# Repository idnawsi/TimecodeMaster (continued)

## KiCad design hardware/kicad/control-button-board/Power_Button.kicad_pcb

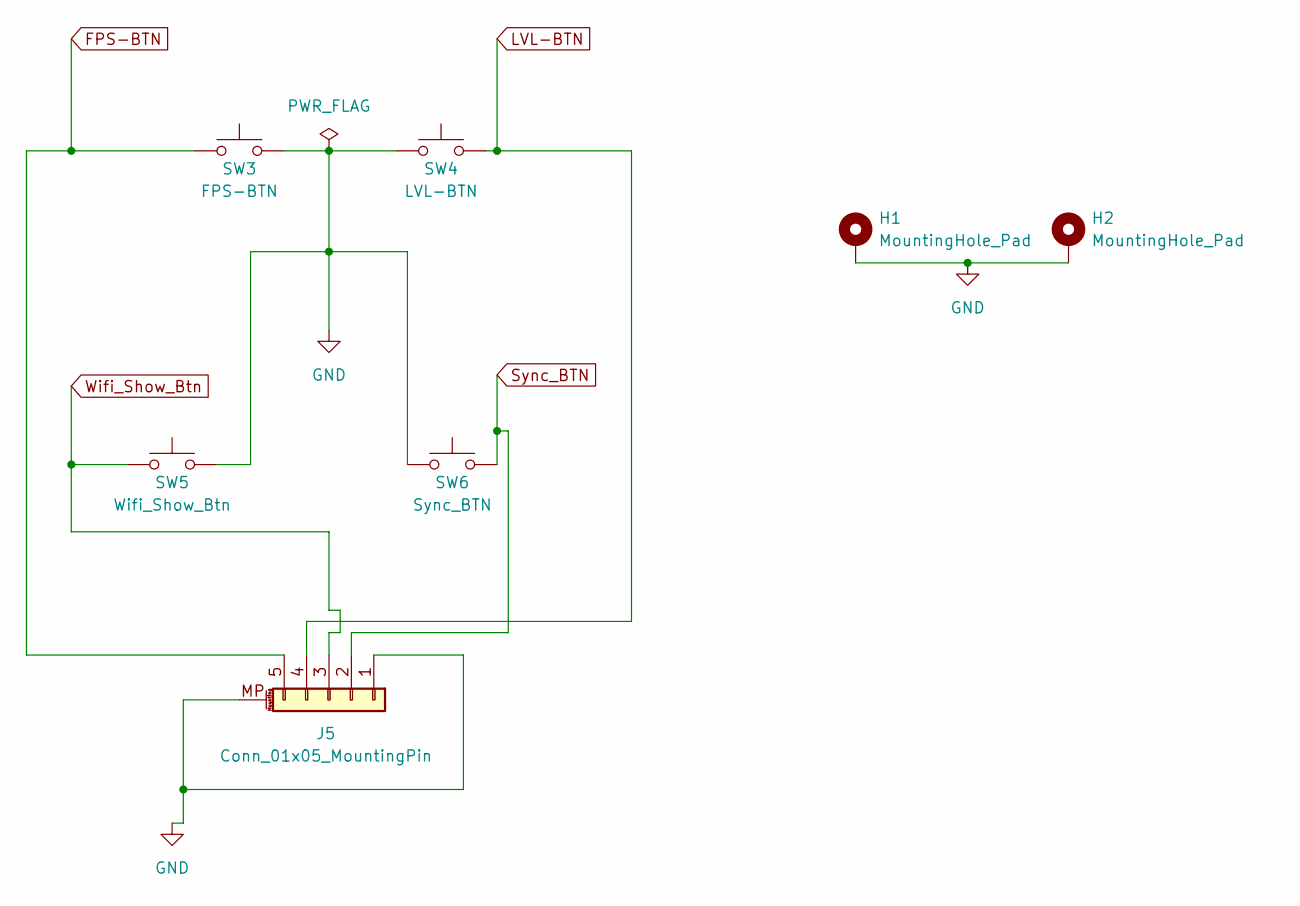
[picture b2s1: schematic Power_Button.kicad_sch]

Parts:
H1, H2: MountingHole_Pad; MountingHole_3.2mm_M3_Pad_Via
J5: Conn_01x05_MountingPin; JST_PH_S5B-PH-SM4-TB_1x05-1MP_P2.00mm_Horizontal
SW3: FPS-BTN; SW_SPST_TL3342
SW4: LVL-BTN; SW_SPST_TL3342
SW5: Wifi_Show_Btn; SW_SPST_TL3342
SW6: Sync_BTN; SW_SPST_TL3342

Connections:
FPS-BTN: J5.5, SW3.1
GND: H1.1, H2.1, J5.1, J5.MP (MountPin), SW3.2, SW4.1, SW5.2, SW6.1
LVL-BTN: J5.4, SW4.2
Sync_BTN: J5.2, SW6.2
Wifi_Show_Btn: J5.3, SW5.1

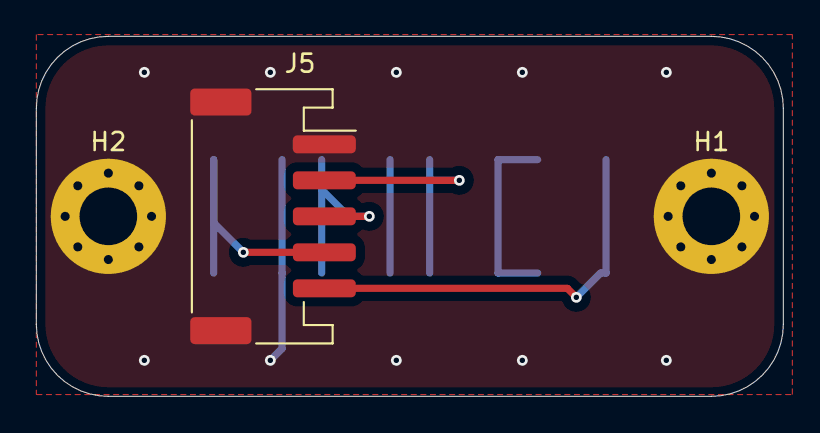
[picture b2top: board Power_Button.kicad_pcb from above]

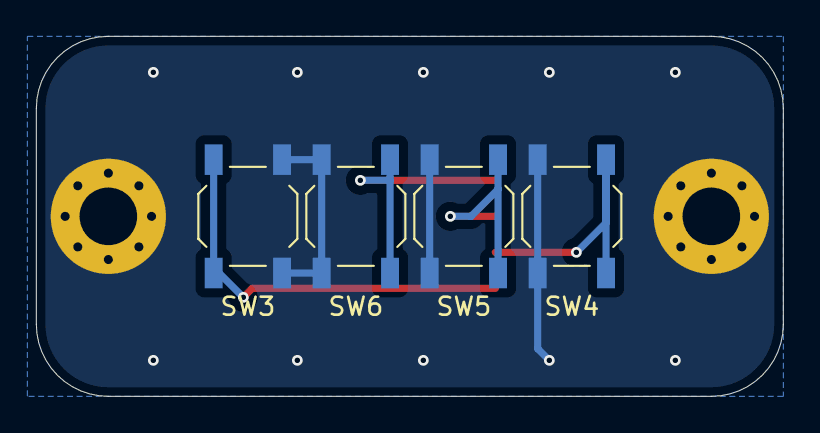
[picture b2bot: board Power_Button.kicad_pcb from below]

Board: 2 copper layers, 41.5 x 20.0 mm, 7 parts (4 on the bottom side), 5 nets.

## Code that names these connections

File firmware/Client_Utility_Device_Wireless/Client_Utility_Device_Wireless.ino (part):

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    }
}

#define SPI_MOSI 13
#define SPI_MISO 12
#define SPI_SCLK 14
#define SPI_CS 15

SPIClass hspi(HSPI);
SPI_Command spiCmd;
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void setupSPI_Master() {
    hspi.begin(SPI_SCLK, SPI_MISO, SPI_MOSI, SPI_CS);
    hspi.setDataMode(SPI_MODE1);
    pinMode(SPI_CS, OUTPUT);
    digitalWrite(SPI_CS, HIGH);
}

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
